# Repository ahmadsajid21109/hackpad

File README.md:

# hackpad

## PCB

## Schemetic

## 3D model

## BOM

4x Switches/Buttons

2x SK6812 MINI LEDs

1x 0.91" 128x32 OLED Display

1x XIAO RP2040

3D Printed Case (2 printed parts - top and bottom case)

1x PCB from JLCPCB

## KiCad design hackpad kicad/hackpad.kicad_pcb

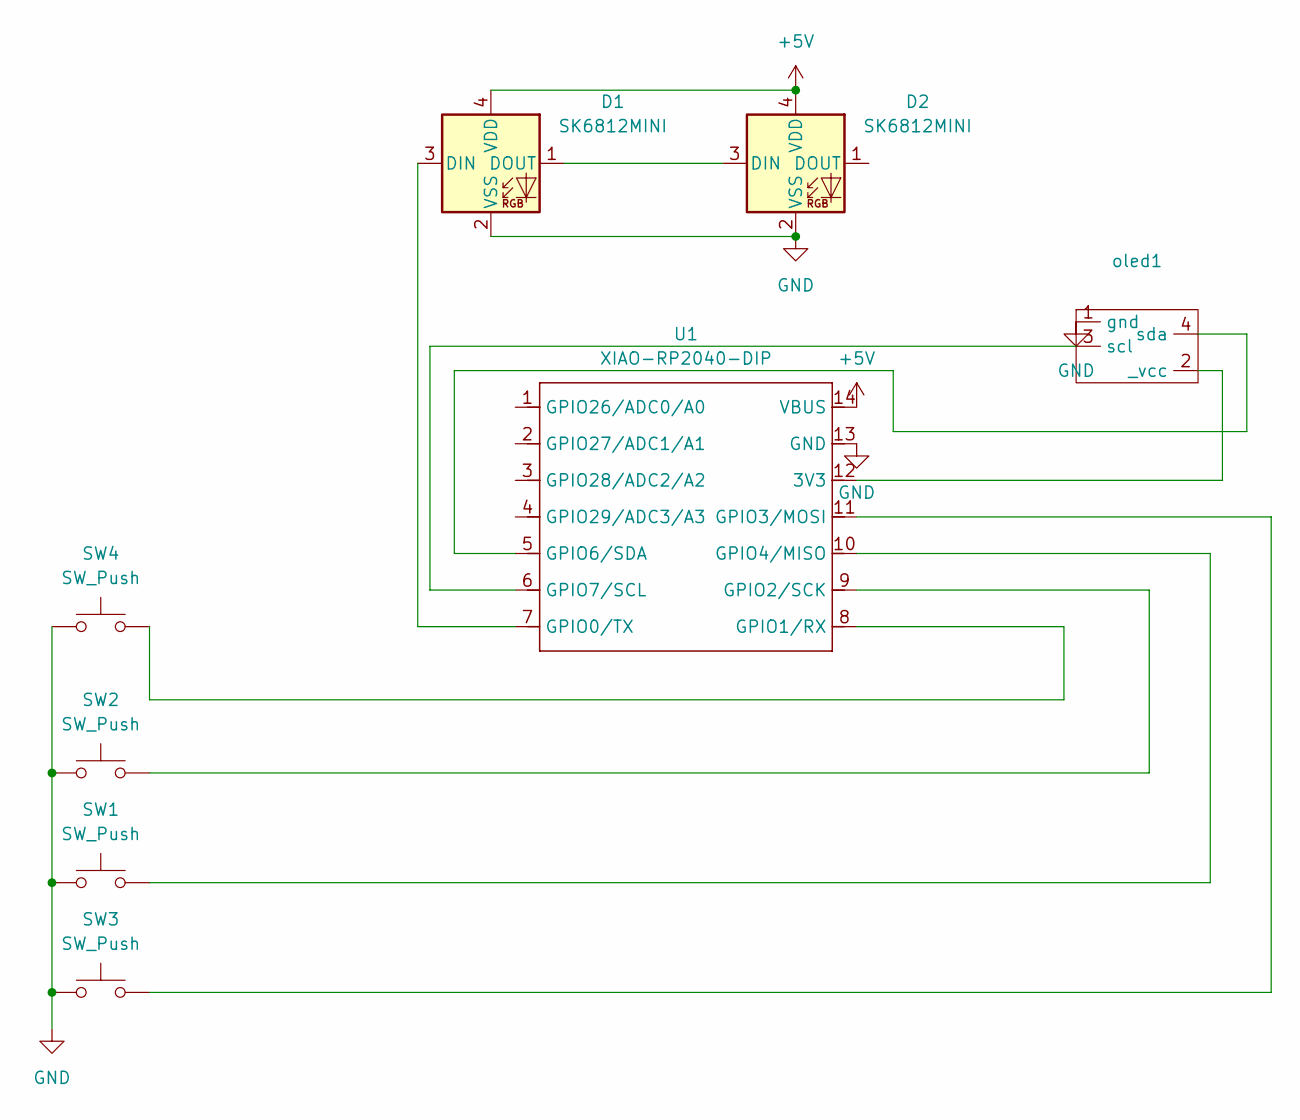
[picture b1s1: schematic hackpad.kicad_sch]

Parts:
D1, D2: SK6812MINI; LED_SK6812MINI_PLCC4_3.5x3.5mm_P1.75mm
SW1, SW2, SW3, SW4: SW_Push; SW_Cherry_MX_1.00u_PCB
U1: XIAO-RP2040-DIP
oled1: SSD1306-0.91-OLED-4pin-128x32

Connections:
+5V: D1.4 (VDD), D2.4 (VDD), U1.14 (VBUS)
GND: D1.2 (VSS), D2.2 (VSS), SW1.1, SW2.1, SW3.1, SW4.1, U1.13 (GND), oled1.1 (gnd)
unnamed: D1.3 (DIN), U1.7 (GPIO0/TX)
unnamed: D1.1 (DOUT), D2.3 (DIN)
unnamed: U1.12 (3V3), oled1.2 (_vcc)
unnamed: SW4.2, U1.8 (GPIO1/RX)
unnamed: SW2.2, U1.9 (GPIO2/SCK)
unnamed: SW3.2, U1.11 (GPIO3/MOSI)
unnamed: SW1.2, U1.10 (GPIO4/MISO)
unnamed: U1.5 (GPIO6/SDA), oled1.4 (sda)
unnamed: U1.6 (GPIO7/SCL), oled1.3 (scl)

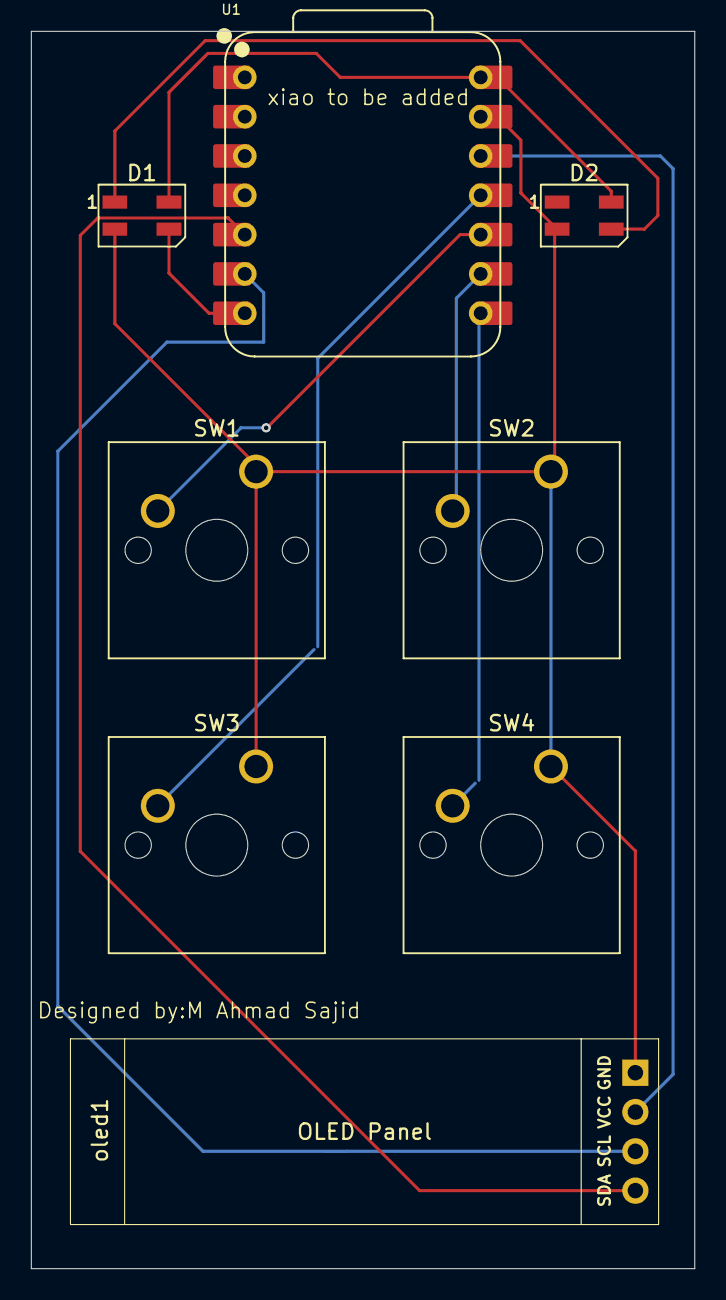
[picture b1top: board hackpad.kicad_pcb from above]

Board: 2 copper layers, 42.9 x 79.9 mm, 8 parts (0 on the bottom side), 11 nets.

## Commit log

2025-12-17 added stuff
    Added detailed sections for PCB, schematic, 3D model, and BOM with images and component list.
2025-12-18 Replace 3D model images with updated screenshots
    Updated 3D model images in the README with new screenshots.
2025-12-18 Add additional screenshots to README
